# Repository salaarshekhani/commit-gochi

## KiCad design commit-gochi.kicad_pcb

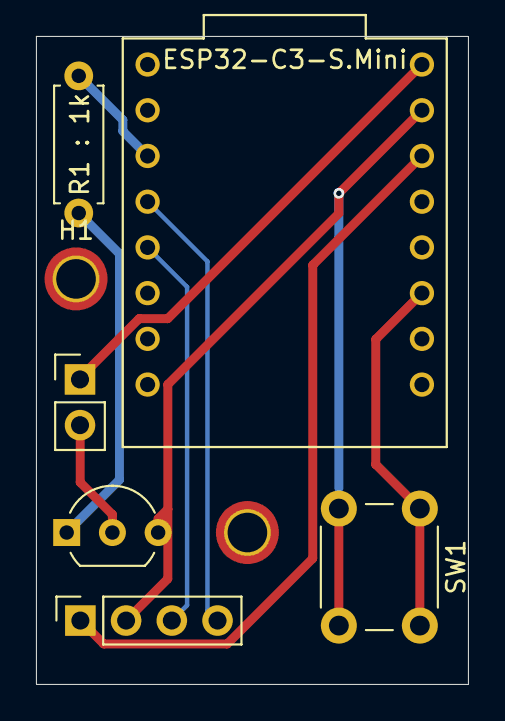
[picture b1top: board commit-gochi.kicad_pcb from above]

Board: 2 copper layers, 24.0 x 36.0 mm, 8 parts (0 on the bottom side), 9 nets.

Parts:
ESP32-C3-S.Mini: ESP32-C3_SUPERMINI_TH; MODULE_ESP32-C3_SUPERMINI_TH
H1, H1#2: MountingHole; MountingHole_2.2mm_M2_ISO7380_Pad_TopBottom
J2: Conn_01x04_Socket; PinSocket_1x04_P2.54mm_Vertical
Q1: Q_NPN_BCE; TO-92_Inline_Wide
R1 : 1k: 1k; R_Axial_DIN0207_L6.3mm_D2.5mm_P7.62mm_Horizontal
SW1: SW_Push; SW_PUSH_6mm
Speaker: Speaker; PinHeader_1x02_P2.54mm_Vertical

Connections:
/BUTTON_IN: ESP32-C3-S.Mini.2 (GPIO2), SW1.1
/OLED_SCL: ESP32-C3-S.Mini.9 (GPIO9), J2.3 (OLED_SCL)
/OLED_SDA: ESP32-C3-S.Mini.8 (GPIO8), J2.4 (OLED_SDA)
/SPEAKER_PWM: ESP32-C3-S.Mini.7 (GPIO7), R1 : 1k.1
unnamed: ESP32-C3-S.Mini.G (GND), J2.2 (GND), Q1.3 (E), SW1.2
unnamed: ESP32-C3-S.Mini.3.3 (3V3), J2.1 (VCC)
unnamed: ESP32-C3-S.Mini.5V, Speaker.1
unnamed: Q1.1 (B), R1 : 1k.2
unnamed: Q1.2 (C), Speaker.2

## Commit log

2026-06-26 PCB, Schematics, BOM.
2026-06-27 Updated BOM w/ prices and links :)
